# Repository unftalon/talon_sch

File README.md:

# talon_sch
Electronic Schematics, libraries, and PCB layouts for the TALON Autonomous Underwater Vehicle

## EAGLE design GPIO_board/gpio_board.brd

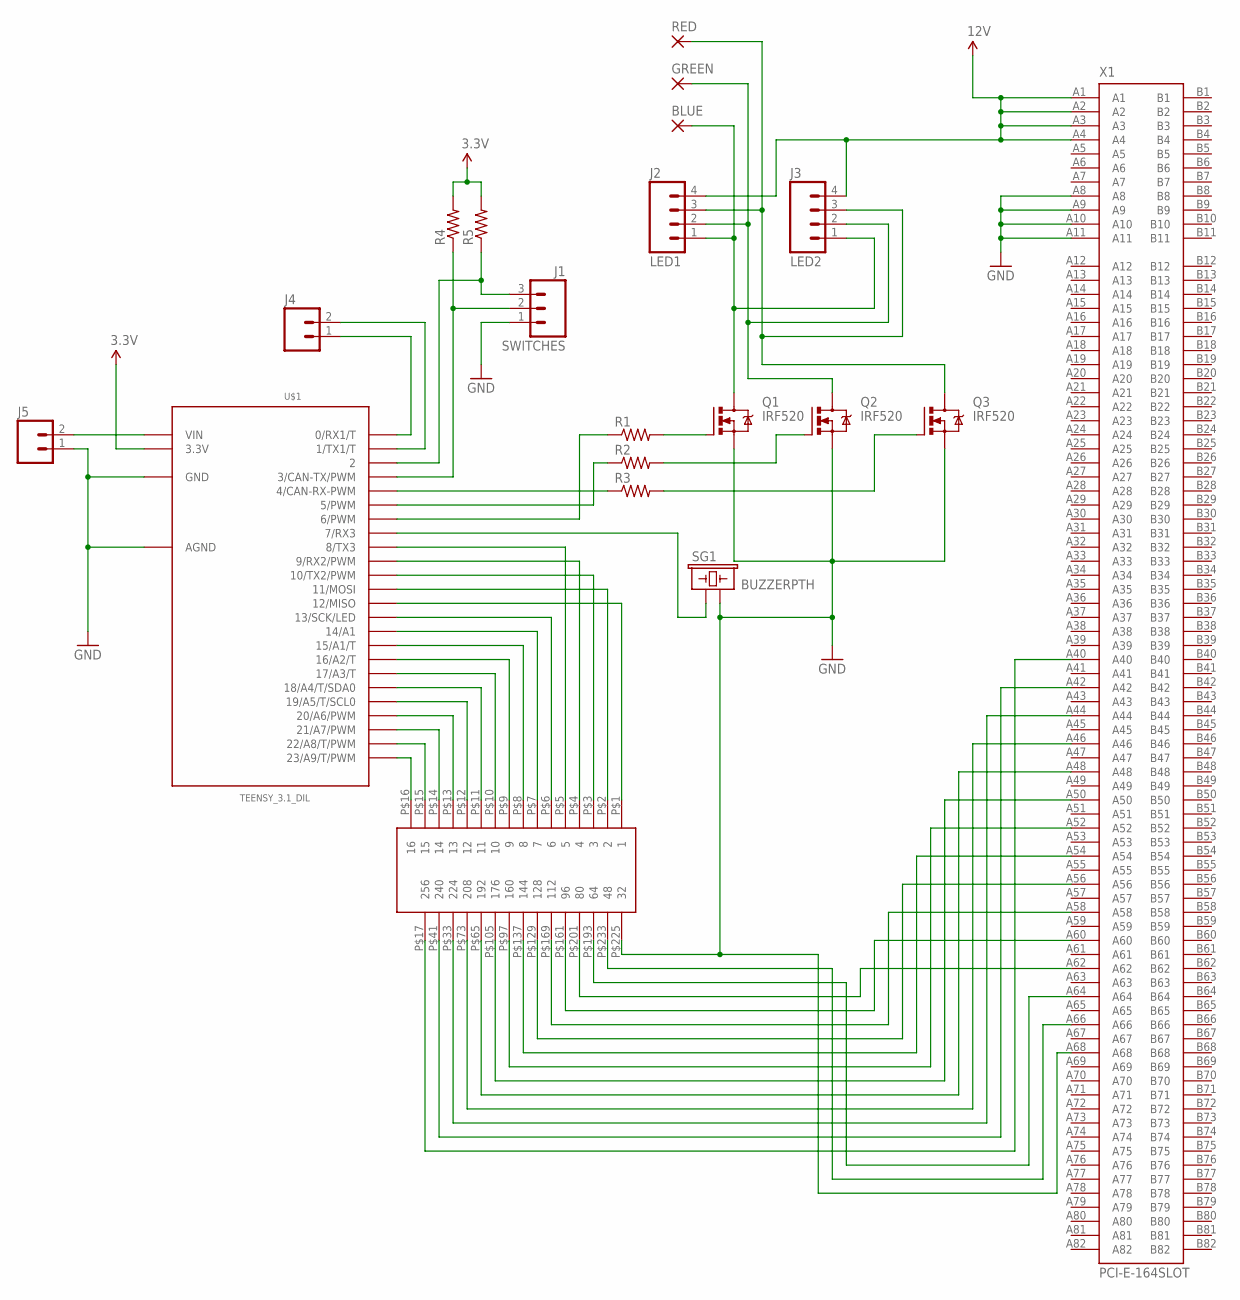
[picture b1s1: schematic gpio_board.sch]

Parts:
BLUE: 2,54/1,0
GREEN: 2,54/1,0
J1: SWITCHES; 1X03
J2: LED1; 1X04
J3: LED2; 1X04
J4, J5: M02PTH; 1X02
Q1, Q2, Q3: IRF520; TO220BV
R1, R2, R3, R4, R5: RESISTOREZ; AXIAL-0.3EZ
RED: 2,54/1,0
SG1: BUZZERPTH; BUZZER-12MM
U$1: TEENSY_3.1_DIL; TEENSY3-DIL
U$2: PROTO_GRID; PROTO_GRID16
X1: PCI-E-164SLOT; PCI-E_SLOT

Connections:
3.3V: R4.P$2 (2), R5.P$2 (2), U$1.3.3V
GND: J1.1, J5.1, Q1.S, Q2.S, Q3.S, SG1.- (2), U$1.AGND, U$1.GND, U$2.P$225 (32), X1.A8, X1.A9, X1.A10, X1.A11, X1.A68
unnamed: Q1.G, R1.P$2 (2)
unnamed: Q2.G, R2.P$2 (2)
unnamed: Q3.G, R3.P$2 (2)
unnamed: J1.3, R5.P$1 (1), U$1.2
unnamed: GREEN.1, J2.2, J3.2, Q2.D
unnamed: J1.2, R4.P$1 (1), U$1.3 (3/CAN-TX/PWM)
unnamed: R3.P$1 (1), U$1.4 (4/CAN-RX-PWM)
unnamed: R2.P$1 (1), U$1.5 (5/PWM)
unnamed: J2.3, J3.3, Q3.D, RED.1
unnamed: R1.P$1 (1), U$1.6 (6/PWM)
unnamed: SG1.+ (1), U$1.7 (7/RX3)
unnamed: U$1.8 (8/TX3), U$2.P$5 (5)
unnamed: U$1.23/A9 (23/A9/T/PWM), U$2.P$16 (16)
unnamed: U$1.22/A8 (22/A8/T/PWM), U$2.P$15 (15)
unnamed: U$1.21/A7 (21/A7/PWM), U$2.P$14 (14)
unnamed: U$1.20/A6 (20/A6/PWM), U$2.P$13 (13)
unnamed: U$1.19/A5 (19/A5/T/SCL0), U$2.P$12 (12)
unnamed: U$1.18/A4 (18/A4/T/SDA0), U$2.P$11 (11)
unnamed: U$1.17/A3 (17/A3/T), U$2.P$10 (10)
unnamed: U$1.16/A2 (16/A2/T), U$2.P$9 (9)
unnamed: U$1.15/A1 (15/A1/T), U$2.P$8 (8)
unnamed: U$1.14/A0 (14/A1), U$2.P$7 (7)
unnamed: U$1.13 (13/SCK/LED), U$2.P$6 (6)
unnamed: U$1.9 (9/RX2/PWM), U$2.P$4 (4)
unnamed: U$1.10 (10/TX2/PWM), U$2.P$3 (3)
unnamed: U$1.11 (11/MOSI), U$2.P$2 (2)
unnamed: U$1.12 (12/MISO), U$2.P$1 (1)
unnamed: J4.1, U$1.0 (0/RX1/T)
unnamed: U$2.P$233 (48), X1.A66
unnamed: U$2.P$193 (64), X1.A64
unnamed: U$2.P$201 (80), X1.A62
unnamed: U$2.P$161 (96), X1.A60
unnamed: U$2.P$169 (112), X1.A58
unnamed: U$2.P$129 (128), X1.A56
unnamed: U$2.P$137 (144), X1.A54
unnamed: U$2.P$97 (160), X1.A52
unnamed: U$2.P$105 (176), X1.A50
unnamed: U$2.P$65 (192), X1.A48
unnamed: U$2.P$73 (208), X1.A46
unnamed: U$2.P$33 (224), X1.A44
unnamed: U$2.P$41 (240), X1.A42
unnamed: U$2.P$17 (256), X1.A40
unnamed: J4.2, U$1.1 (1/TX1/T)
unnamed: J5.2, U$1.VIN
unnamed: BLUE.1, J2.1, J3.1, Q1.D
VCC: J2.4, J3.4, X1.A1, X1.A2, X1.A3, X1.A4

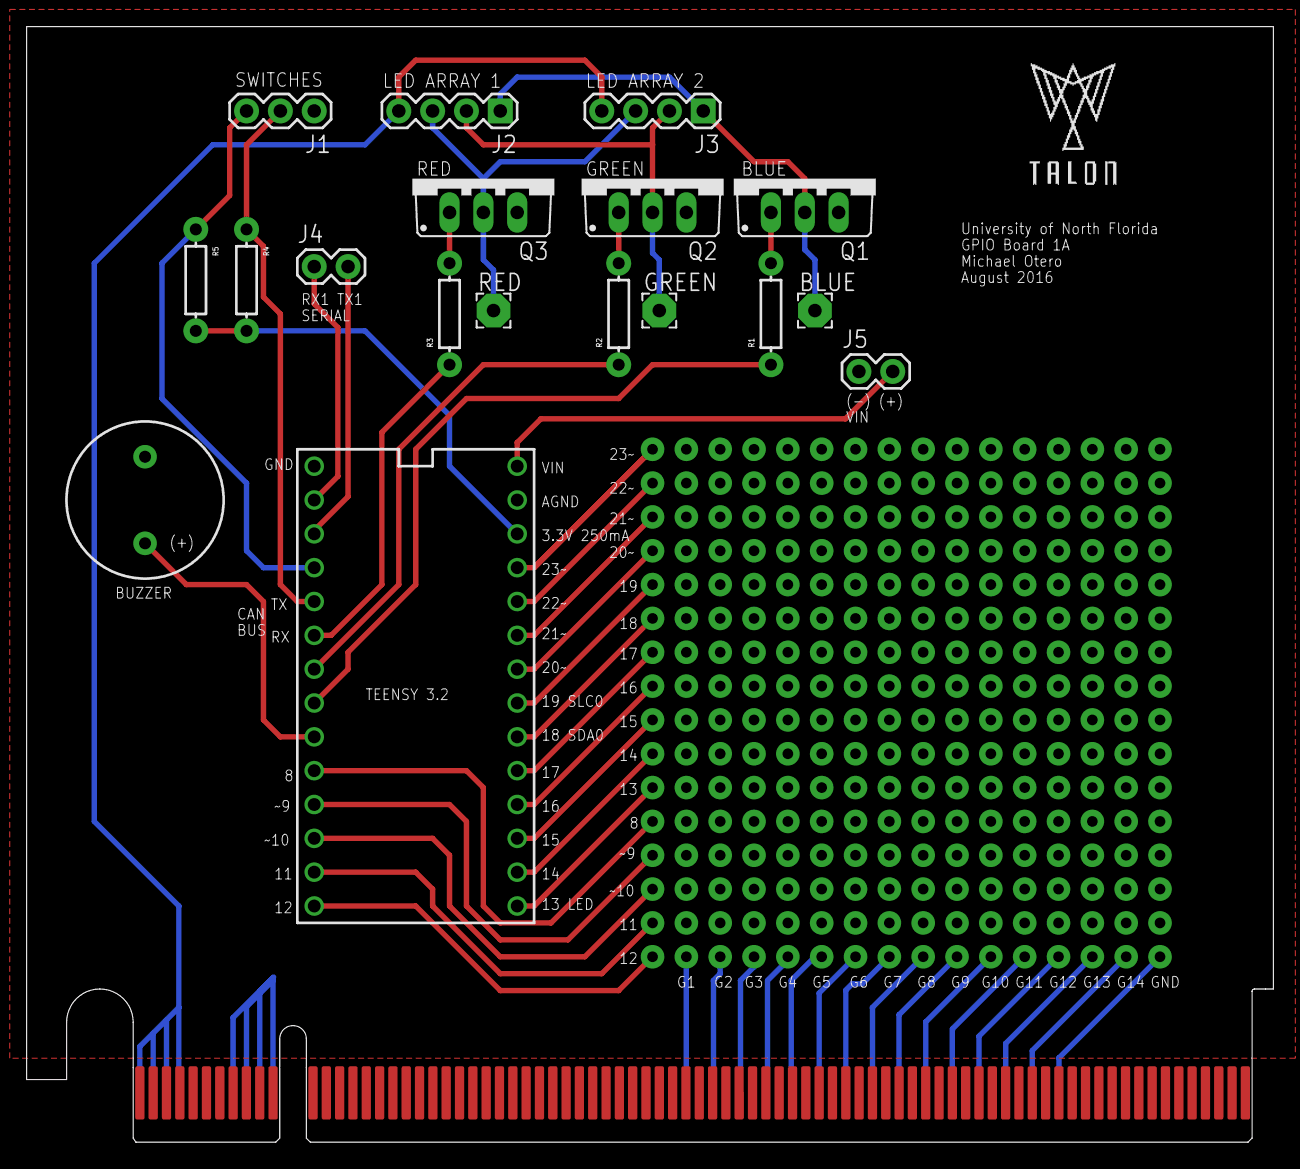
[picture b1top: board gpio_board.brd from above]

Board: 2 copper layers, 93.6 x 83.8 mm, 20 parts (1 on the bottom side), 48 nets.

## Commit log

2016-07-29 updated for lck files
2016-07-29 routed some things
    not final. need to finish outline and dimensions of board. need to
    determine what other things need to go through the PCI connector (If
    any).
2016-07-29 added sides. need to figure out discontinuity with PCIe connector
2016-07-30 routed all connections
2016-07-30 removed dimension lines
2016-07-31 fixed board outline and fixed some traces
    figured out that the PCIe slot is in metric, so that requires metric
    grid to get it aligned right.
2016-08-02 updated gitignore so it actually works
2016-08-02 test change
2016-08-02 figured out ground planes
    or did I? ???
2016-08-02 routed some red traces.
    GO RED TEAM
2016-08-02 routed some wires
2016-08-02 SUCCESSfully made two ground pours
2016-08-02 added botom pins to proto grid
2016-08-02 removed extra pin, assigned pins to package
2016-08-02 confirmed connected pins
2016-08-02 connected a bunch of things to a bunch of things
2016-08-02 something has gone horribly wrong.
    assuming that all the pads in the PROTO_GRID package where placed
    perfectly chronologically has resulted in a tragic waste of 30 minutes.
    Apparently I couldn't just assume the entire bottom row was multiples of
    16. :-1:
2016-08-02 figured out mess
    too bad the numbers on the schematic symbol now mean nothing. ha ha ha
    ha :|
2016-08-02 up means down and down means up
2016-08-02 what is left is right, and right is left
2016-08-02 re-routed wires so i could stop f***ing getting mixed up on orientation
2016-08-02 saving before autorouting
2016-08-02 fixed traces from PCIe slot to proto_grid
2016-08-02 added ground pad to proto grid
2016-08-02 added headers for VIN and serial port. fixed issues with redundant manual route to ground from pin 1 on teensy.
2016-08-02 fitment check
2016-08-04 changed the footprint of the PCIe connector and broke the ground planes
2016-08-05 fixed ground pour problem
2016-08-05 did DRC, everything looks good...
2016-08-05 added silkscreen logo
2016-08-05 labeled some parts
2016-08-05 initial commit
    about to submit these to advanced circuits to determine if they're
    worthy
2016-08-08 not ignoring epf files
2016-08-08 added breakout pads for RGB LED drivers
2016-09-05 Testing push

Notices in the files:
parts and their libraries:
SparkFun-Connectors: Licensing: Creative Commons ShareAlike 4.0 International - https://creativecommons.org/licenses/by-sa/4.0
